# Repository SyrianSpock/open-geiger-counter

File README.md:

open-geiger-counter
===================

Description
-----------

The <a href="http://opengeiger.de/index_en.html">Open geiger</a> project aims to give access to cheap geiger counters for the masses.
This is an attempt at making such a cheap geiger counter - using PIN diodes and following the design of the 'Stuttgarter Geigerle'- in a smaller size form.
In this repository are made available the production files for the realisation of such a cheap pocket geiger counter:
  * <a href="open-geiger-counter/schematic.pdf">Schematic</a>
  * <a href="open-geiger-counter/kicad">Kicad files</a>
  * <a href="open-geiger-counter/gerber">Gerber files</a>
  * 3D printed case (TBD)

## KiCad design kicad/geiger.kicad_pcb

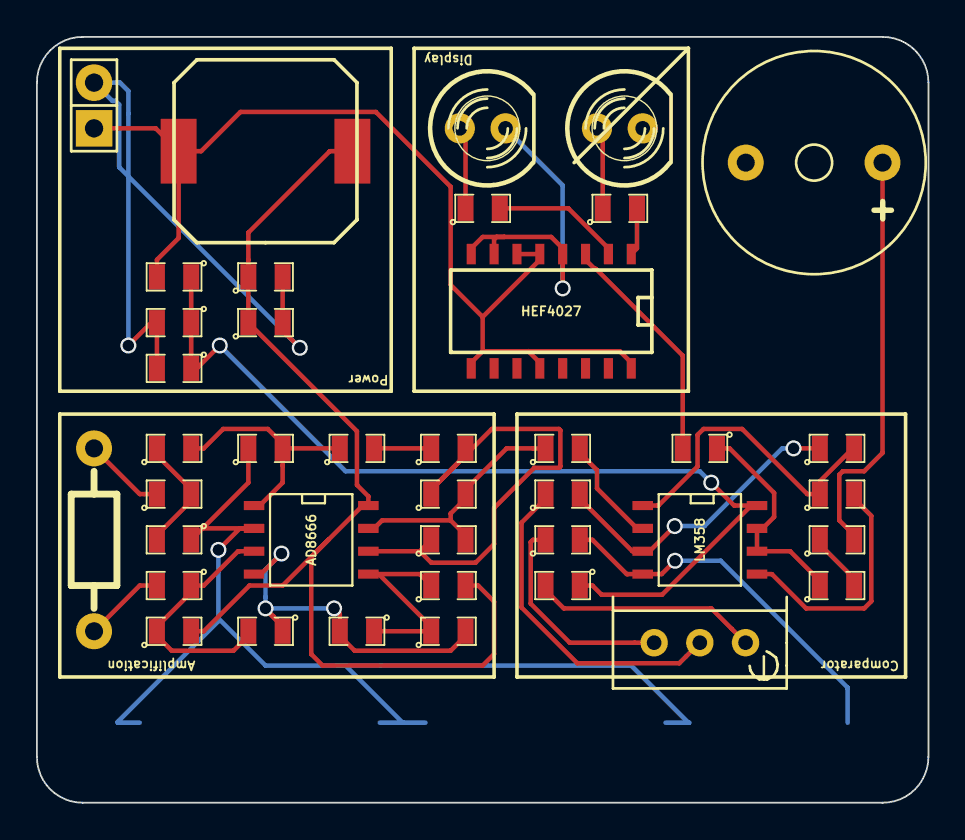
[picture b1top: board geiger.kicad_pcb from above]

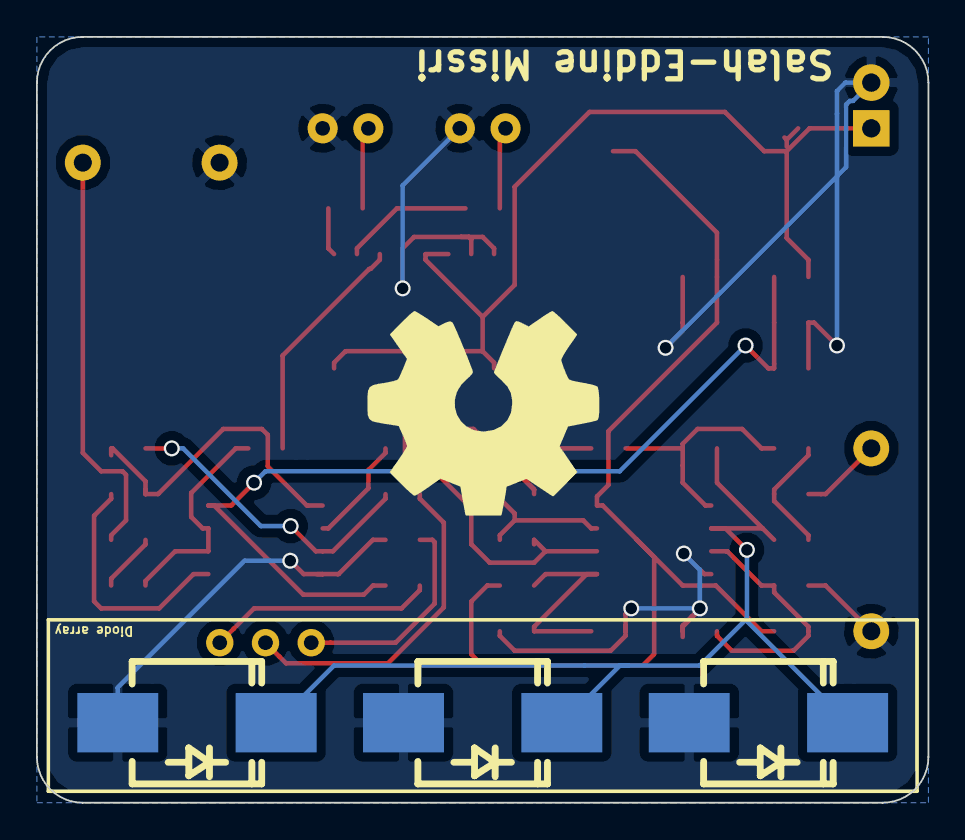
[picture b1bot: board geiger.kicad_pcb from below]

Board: 2 copper layers, 49.5 x 42.5 mm, 43 parts (3 on the bottom side), 28 nets.

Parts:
BT1: BATTERY; Pin_Header_Straight_1x02
C1, C3, C4, C6, C7, C12, C13: 100n; SMD-0805
C2, C5: 47u; SMD-0805
C8, C10, C14: 10p; SMD-0805
C9: 50p; SMD-0805
C11: 50p; Resistor_Horizontal_RM10mm
D1, D2, D3: BPW34; Diode-SMC_Handsoldering
D4: red; LED-5MM
D5: green; LED-5MM
L1: 1mH; self_cms_we-tpc_XL
R1, R2, R8: 4.7k; SMD-0805
R3: 47; SMD-0805
R4, R5, R6, R7, R11, R12, R15, R16: 1k; SMD-0805
R9: 15k; SMD-0805
R10: 10M; SMD-0805
R13, R14: 10k; SMD-0805
R17: 100k; SMD-0805
RV1: 5k; Potentiometer_Bourns_3296W_3-8Zoll_Inline_ScrewUp
SP1: SPEAKER; Buzzer_12x9.5RM7.6
U1: LM358; SOIC-8-N
U2: AD8666; SOIC-8-N
U3: HEF4027; SO-16-N

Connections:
+BATT: BT1.1, L1.2, R3.2, U3.5, U3.6, U3.9, U3.12, U3.16
GND: BT1.2, C1.2, C2.2, C4.2, C5.2, C7.2, C11.2, C13.2, D1.1, D2.1, D3.1, D4.2, D5.2, R2.2, R9.1, R14.2, SP1.2, U1.4, U2.4, U3.4, U3.7, U3.8
unnamed: C3.1, R4.2, U1.3
unnamed: C3.2, R6.1, U1.1
unnamed: C6.1, R7.2
unnamed: C6.2, SP1.1
unnamed: C7.1, R8.1, R9.2, U2.3
unnamed: C8.2, C9.2, C10.1
unnamed: C10.2, C12.1, R10.2, U2.1
unnamed: C9.1, C11.1
unnamed: C12.2, R12.1
unnamed: C13.1, R13.1, R14.1, U2.5
unnamed: C14.1, R12.2, R17.1, U2.6
unnamed: D4.1, R15.1
unnamed: D5.1, R16.1
unnamed: R1.2, RV1.1
unnamed: R2.1, RV1.3
unnamed: R4.1, RV1.2
unnamed: R5.2, U1.2
unnamed: R6.2, U1.5
unnamed: R11.2, U3.3
unnamed: R15.2, U3.2
unnamed: R16.2, U3.1
VCC: C4.1, C5.1, L1.1, R8.2, R13.2, U2.8
VDD: C1.1, C2.1, R1.1, R3.1, U1.8
amp_out: C14.2, R5.1, R17.2, U2.7
out: R7.1, R11.1, U1.6, U1.7
raw: C8.1, D1.2, D2.2, D3.2, R10.1, U2.2

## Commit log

2014-10-27 open geiger counter documentation
2015-02-03 Clean up backup files
